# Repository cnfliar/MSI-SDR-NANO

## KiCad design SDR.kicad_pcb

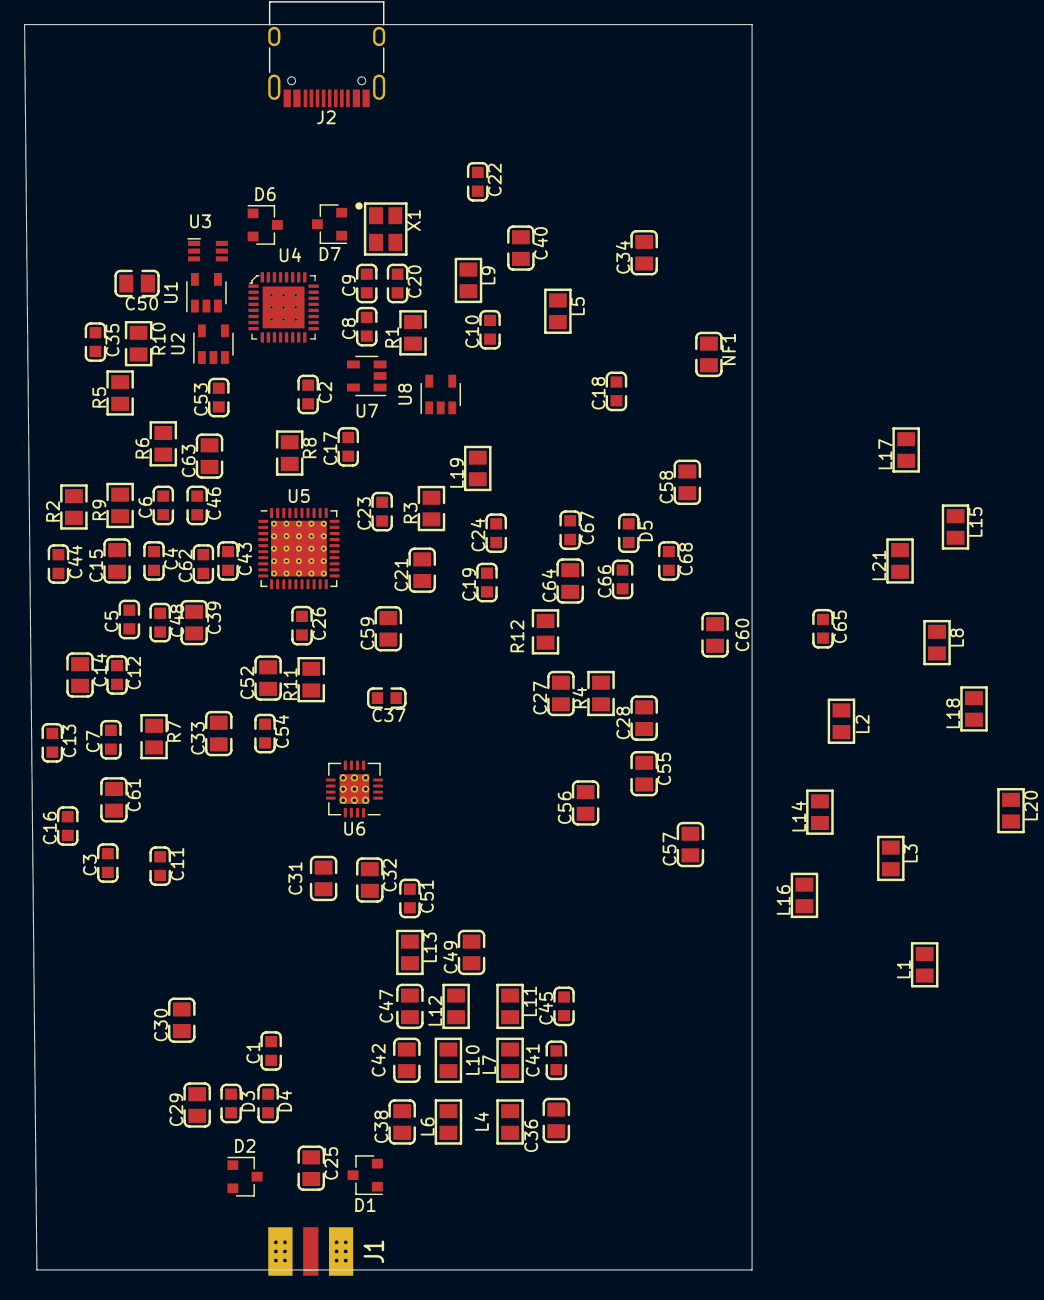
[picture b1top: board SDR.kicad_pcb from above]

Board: 2 copper layers, 59.9 x 102.6 mm, 120 parts (0 on the bottom side), 84 nets, no tracks yet.

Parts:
C1, C4, C6, C7, C8, C10, C11: 1UF; 0603_C
C2, C16, C17, C18, C22, C26, C43, C44, C46, C48, C51, C53, C62: 10NF; 0603_C
C3: 0.1UF; 0603_C
C5, C12, C13, C19, C20, C65, C66, C67, C68: 10UF; 0603_C
C9: 15NF; 0603_C
C14, C15, C21, C29, C30, C64: 0.1UF; 0805_C
C23: 6800PF; 0603_C
C24: 33NF; 0603_C
C25: 100NF; 0805_C
C27, C28, C50, C52: 5.6PF; 0805_C
C31, C32, C56, C63: 10PF; 0805_C
C33, C58, C59: 1.8PF; 0805_C
C34, C55: 27PF; 0805_C
C35, C37: 1NF; 0603_C
C36, C49: 12PF; 0805_C
C38, C47: 110PF; 0805_C
C39, C61: 1.5PF; 0805_C
C40: 39PF; 0805_C
C41, C45: 15PF; 0603_C
C42: 100PF; 0805_C
C54: 4.7PF; 0603_C
C57: 22PF; 0805_C
C60: 2.2PF; 0805_C
D1, D2, D6, D7: BAV99; SOT-23
D3, D4: D; 0603_C
D5: LED; 0603_C
J1: ANT; SMA_OPL_EM
J2: USB_C_Receptacle_USB2.0; USB_C_Receptacle_HRO_TYPE-C-31-M-12
L1: 15NH; 0805_L
L2: 68NH; 0805_L
L3: 33NH; 0805_L
L4, L13: 220NH; 0805_L
L5, L19: 100NH; 0805_L
L6, L15: 22NH; 0805_L
L7, L11: 180NH; 0805_L
L8: 47NF; 0805_L
L9: 270NH; 0805_L
L10: 27NH; 0805_L
L12: 22NF; 0805_L
L14: 82NH; 0805_L
L16: 39NH; 0805_L
L17, L18: 6.8NH; 0805_L
L20: 8.2NH; 0805_L
L21: 600R-100M; 0805_L
NF1: NF; 0805_C
R1: 10k; 0805_R
R2: 510R; 0805_R
R3: 390R; 0805_R
R4, R6, R9, R11: 33R; 0805_R
R5, R10: 18R; 0805_R
R7, R8: 10K; 0805_R
R12: 47K; 0805_R
U1, U2: SN74LVC1G00; SOT-23-5
U3: SN74LVC1G386; SC70-6
U4: msi2500; QFN-32-1EP_5x5mm
U5: msi001-RESCUE-msisdr; QFN-40-1EP_6x6mm_P0.5mm_EP4.6x4.6mm_ThermalVias
U6: PE42641; QFN-16-1EP_4x4mm_P0.5mm_EP2.45x2.45mm_ThermalVias
U7, U8: RP112N331D; SOT-23-5
X1: 24MHZ; SMD-3225_4P

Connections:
AMP2IN: C51.1, U5.40
AMP2INB: C53.1, U5.39
B3IN: C63.2, U5.3
B3INB: C62.1, U5.4
B3LBAND: C35.1, C50.2, R9.2
B45IN: C43.1, U5.6
B45INB: C48.1, U5.7
GND: C1.1, C3.1, C4.1, C5.1, C6.1, C7.1, C8.1, C10.2, C11.2, C12.2, C13.2, C14.2, C15.2, C16.2, C18.1, C19.2, C20.2, C21.2, C22.2, C26.2, C29.1, C30.2, C33.2, C34.2, C36.2, C41.2, C45.2, C46.2, C48.2, C49.2, C53.2, C55.2, C57.2, C59.2, C61.2, C62.2, C64.2, C65.2, C66.2, C67.2, C68.2, D1.1, D2.2, D5.1, D6.1, D7.1, J1.2, J1.3, J2.A1, J2.A12, J2.B1, J2.B12, L8.2, L9.2, L16.2, L17.2, NF1.1, R2.1, R5.2, R10.2, U1.3, U2.3, U3.2, U4.8, U4.28, U4.29, U4.30, U4.33, U5.41, U6.1, U6.5, U6.7, U6.9, U6.10, U6.12, U6.14, U6.17, U7.2, U8.2, X1.2
GPIO0: R8.1, U2.1, U3.1, U4.2
GPIO2: R7.1, U2.2, U3.3, U4.4
I-IN-N: U4.10, U5.12
I-IN-P: U4.9, U5.11
LBAND-IN: C59.1, L18.2, L20.2, U5.24
LBAND-INB: C60.2, L20.1, U5.25
unnamed: C2.1, U4.6
unnamed: C2.2, U4.7
unnamed: C5.2, U4.13
unnamed: C8.2, U4.16
unnamed: C9.1, U4.22
unnamed: C9.2, X1.3
unnamed: C10.1, U4.17
unnamed: C12.1, C13.1, C14.1, C15.1, U5.1, U5.2, U5.8
unnamed: C17.1, U5.20
unnamed: C20.1, C22.1, U5.23, U5.29, U5.30
unnamed: C23.1, C24.2, U5.27
unnamed: C23.2, R3.2, U5.28
unnamed: C24.1, R3.1, U5.26
unnamed: C25.1, D1.2, D2.1, U6.11
unnamed: C25.2, J1.1
unnamed: C27.1, C28.2, R4.1, R5.1, R6.2
unnamed: C28.1, L1.2, L2.2, R6.1
unnamed: C29.2, D3.1, R7.2, U6.4
unnamed: C30.1, D4.1, R8.2, U6.3
unnamed: C31.1, U6.8
unnamed: C31.2, C32.2, C38.2, L4.1, L6.2
unnamed: C32.1, U6.6
unnamed: C33.1, L1.1, L3.2
unnamed: C34.1, L2.1, L5.2
unnamed: C35.2, U6.13
unnamed: C36.1, L4.2
unnamed: C37.2, U6.15
unnamed: C38.1, C42.2, L6.1, L7.1, L10.2
unnamed: C39.1, C43.2, L8.1
unnamed: C39.2, L3.1
unnamed: C40.1, C44.1, L9.1
unnamed: C40.2, L5.1
unnamed: C41.1, L7.2
unnamed: C42.1, C47.2, L10.1, L11.1, L12.2
unnamed: C45.1, L11.2
unnamed: C47.1, C51.2, L12.1, L13.1
unnamed: C49.1, L13.2
unnamed: C50.1, C52.2, R9.1, R10.1, R11.2
unnamed: C52.1, C54.2, L14.2, R11.1
unnamed: C54.1, C58.2, L15.1, L18.1, NF1.2
unnamed: C55.1, L15.2
unnamed: C56.1, C57.1, L16.1, L19.1
unnamed: C56.2, L14.1
unnamed: C58.1, C60.1, L17.1
unnamed: C61.1, C63.1, L19.2
unnamed: D5.2, R12.2
unnamed: R1.1, X1.1
unnamed: R2.2, U4.21
unnamed: U1.1, U2.4
unnamed: U1.2, U3.4
unnamed: U3.6, U4.5
Q-IN-N: U4.12, U5.21
Q-IN-P: U4.11, U5.22
REFCLK: C17.2, U4.24
SP3: D3.2, D4.2, U1.4
SPICLK: U4.27, U5.34
SPIDATA: U4.26, U5.35
SPIEN: U4.25, U5.33
USBDM: J2.A7, J2.B7, U4.20
USBDP: D6.3, D7.3, J2.A6, J2.B6, U4.19
V18-SYNTH: C6.2, U4.15, U7.3
VCC2V8: C16.1, C19.1, C21.1, C26.1, C67.1, U5.14, U5.15, U5.18, U5.19, U5.32, U5.36, U6.2, U7.5
VCC3V3: C3.2, C4.2, C11.1, C68.1, D6.2, D7.2, R1.2, U4.14, U4.18, U4.32, U8.5, X1.4
VCC5V: C64.1, C65.1, C66.1, L21.2, U7.1, U8.1, U8.3
VCC50USB: J2.A4, J2.A9, J2.B4, J2.B9, L21.1, R12.1
VCCGPIO1V8: C1.2, U1.5, U2.5, U3.5, U4.1
VDDI1V8: C7.2, C18.2, U4.31, U5.31
VHFB45: C27.2, C37.1, R4.2
VHFIN: C44.2, U5.10
VHFINB: C46.1, U5.9

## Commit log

2020-07-25 Add files via upload
    kicad 只把图画好，pcb还没画好
